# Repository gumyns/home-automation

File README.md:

# Licenses
Code: [Apache 2.0](./LICENSE) ([tl;dr](https://choosealicense.com/licenses/apache-2.0/))

PCB: [CC-BY](./CC-BY.md) ([tl;dr](https://creativecommons.org/licenses/by/4.0/))

# What is it?
STM32 ARM based home automation system. Devices are built with STM32 F0 series microcontrollers (mostly with [STM32F030F4](http://www.st.com/en/microcontrollers/stm32f0x0-value-line.html?querycriteria=productId=LN1826), cheapest one). Project provides also a plugin for [OpenHab2](http://docs.openhab.org/) ([demo](http://demo.openhab.org:8080/start/index)), that allows integration also with other automation systems.

## Architecture
Generally it looks like this:

computer <=> gateway <=> hub <=> device 

On top there's a computer with OpenHab2 running with plugin configured (e.g. PC, RaspberryPi, Odroid, whatever that can run Java8).

Gateway is some cheap ARM based board with Linux, like Rasperry Zero, NanoPi, and communicates with central computer utilizing distributed system built on top of TCP/IP.

Hub is an ARM based board, that can communicate with gateway using any of supported protocols, and can communicate with devices. Amount of ports is configurable.

Device is just a worker (also ARM based board), that communitates with hubs using specific protocol, and provides data to the system.

#### This repository contains following modules
##### - [OpenHab2 plugin](./openhab2)
##### - [C++ server and plugins for gateways](./server)
##### - [PCB layouts and microcontrollers code](./hardware)

# NOTE
This project is in early stage, it's already a working prototype but far from final product.

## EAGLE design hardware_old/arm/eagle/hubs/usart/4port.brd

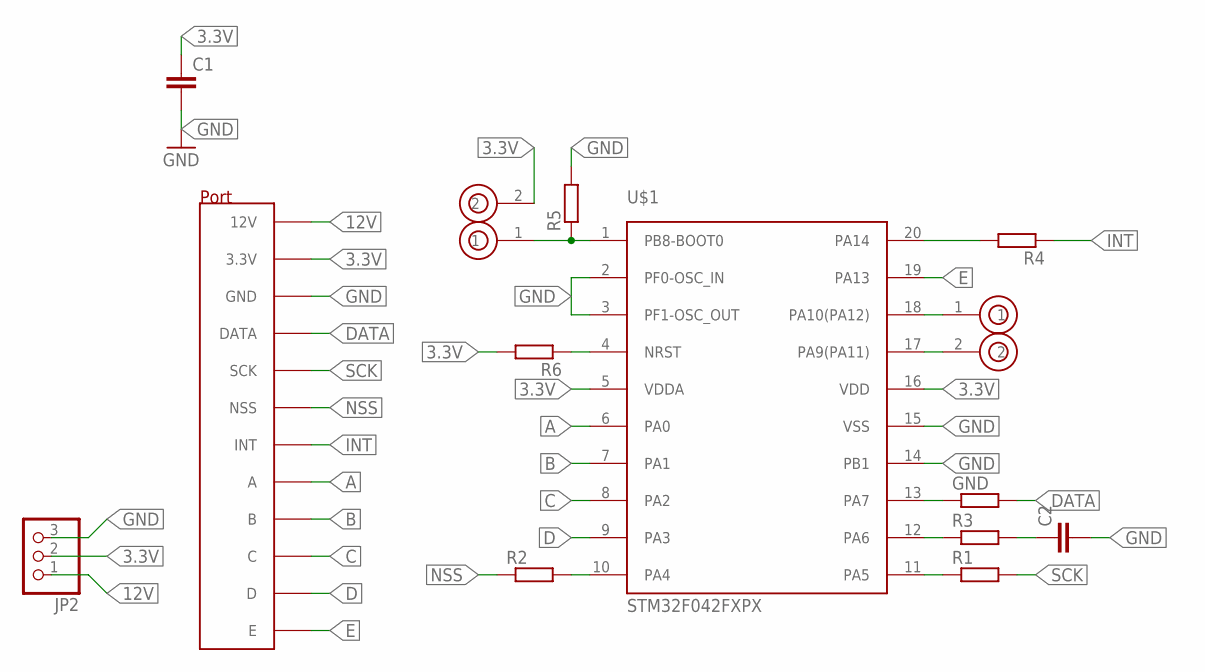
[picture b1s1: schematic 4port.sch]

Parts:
C1, C2: C-EUC1206; C1206
GND: R-EU_R0603; R0603
JP2: PINHD-1X3; 1X03
R1, R2, R3, R4, R5, R6: R-EU_R0603; R0603
U$1: STM32F042FXPX; TSSOP20
U$2, U$3: GOLDPIN_2; GOLDPIN_2_SMD
U$4: HUB_PORT

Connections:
3.3V: C1.1, JP2.2, R6.2, U$1.5 (VDDA), U$1.16 (VDD), U$2.2, U$4.3.3V
12V: JP2.1, U$4.12V
A: U$1.6 (PA0), U$4.A
B: U$1.7 (PA1), U$4.B
C: U$1.8 (PA2), U$4.C
D: U$1.9 (PA3), U$4.D
DATA: GND.2, U$4.DATA
E: U$1.19 (PA13), U$4.E
GND: C1.2, C2.2, JP2.3, R5.2, U$1.2 (PF0-OSC_IN), U$1.3 (PF1-OSC_OUT), U$1.14 (PB1), U$1.15 (VSS), U$4.GND
INT: R4.1, U$4.INT
unnamed: C2.1, R3.2
unnamed: GND.1, U$1.13 (PA7)
unnamed: R3.1, U$1.12 (PA6)
unnamed: R1.1, U$1.11 (PA5)
unnamed: R2.2, U$1.10 (PA4)
unnamed: R6.1, U$1.4 (NRST)
unnamed: R5.1, U$1.1 (PB8-BOOT0), U$2.1
unnamed: U$1.18 (PA10(PA12)), U$3.1
unnamed: U$1.17 (PA9(PA11)), U$3.2
unnamed: R4.2, U$1.20 (PA14)
NSS: R2.1, U$4.NSS
SCK: R1.2, U$4.SCK

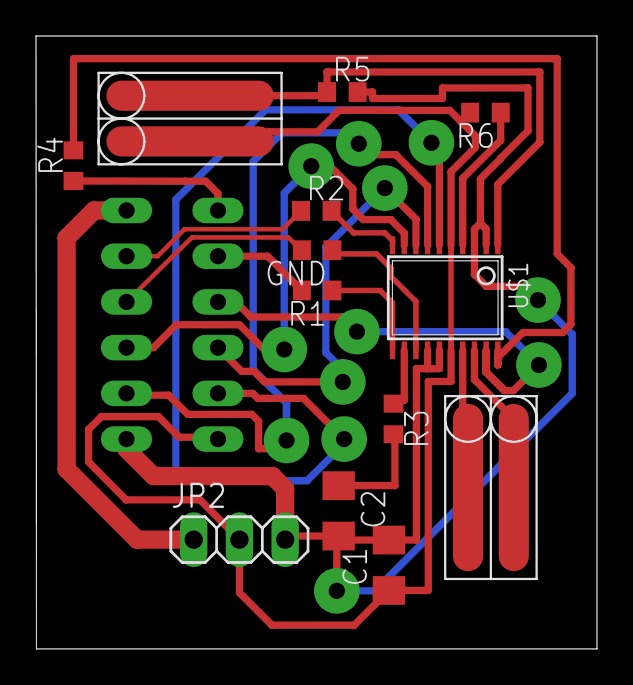
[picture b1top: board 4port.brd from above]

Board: 2 copper layers, 31.2 x 34.1 mm, 14 parts (1 on the bottom side), 22 nets.

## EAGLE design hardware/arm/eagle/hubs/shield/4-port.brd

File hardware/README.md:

## Prerequisites
Download gcc-arm: http://gnuarmeclipse.github.io/toolchain/install/

Generate toolchains and cmake files, call this:
```commandline
python prepare.py
```

Download CubeMX package for STM32F0, or whole STM32CubeMX
```
http://www.st.com/en/embedded-software/stm32cubef0.html
```

## Building
Setup proper toolchain for correct device:
```commandline
mkdir build 
cd build 
cmake .. -DCMAKE_TOOLCHAIN_FILE=../toolchains/STM32F030x6.cmake
```

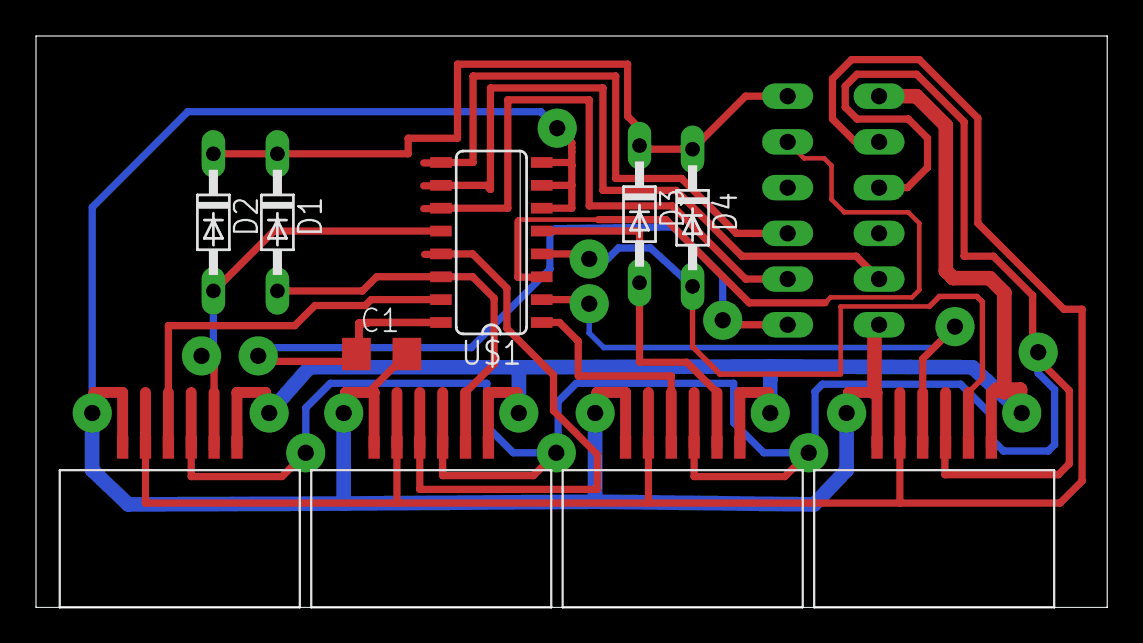
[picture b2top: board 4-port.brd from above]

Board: 2 copper layers, 59.5 x 31.7 mm, 11 parts (0 on the bottom side), 18 nets.

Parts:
C1: C1206
D1, D2, D3, D4: BAS15; DO34-7
U$1: 74HC4051_MUX; SO16
U$2, U$4, U$5, U$7: RJ12SMD; RJ12_SMD
U$3: HUB_PORT

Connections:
3.3V: C1.1, U$1.16, U$3.3.3V
12V: U$2.VCC, U$3.12V, U$4.VCC, U$5.VCC, U$7.VCC
A: U$1.11, U$3.A
B: U$1.10, U$3.B
C: U$1.9, U$3.C
DATA: U$2.DATA, U$3.DATA, U$4.DATA, U$5.DATA, U$7.DATA
GND: C1.2, U$1.6, U$1.7, U$1.8, U$2.GND, U$3.GND, U$4.GND, U$5.GND, U$7.GND
INT: D1.C, D2.C, D3.C, D4.C, U$3.INT
INT0: D1.A, U$1.14, U$2.INT
INT1: D2.A, U$1.12, U$4.INT
INT2: D3.A, U$1.5, U$5.INT
INT3: D4.A, U$1.4, U$7.INT
NSS: U$2.NSS, U$3.NSS, U$4.NSS, U$5.NSS, U$7.NSS
SCK: U$1.3, U$3.SCK
SCK0: U$1.13, U$2.SCK
SCK1: U$1.15, U$4.SCK
SCK2: U$1.1, U$5.SCK
SCK3: U$1.2, U$7.SCK

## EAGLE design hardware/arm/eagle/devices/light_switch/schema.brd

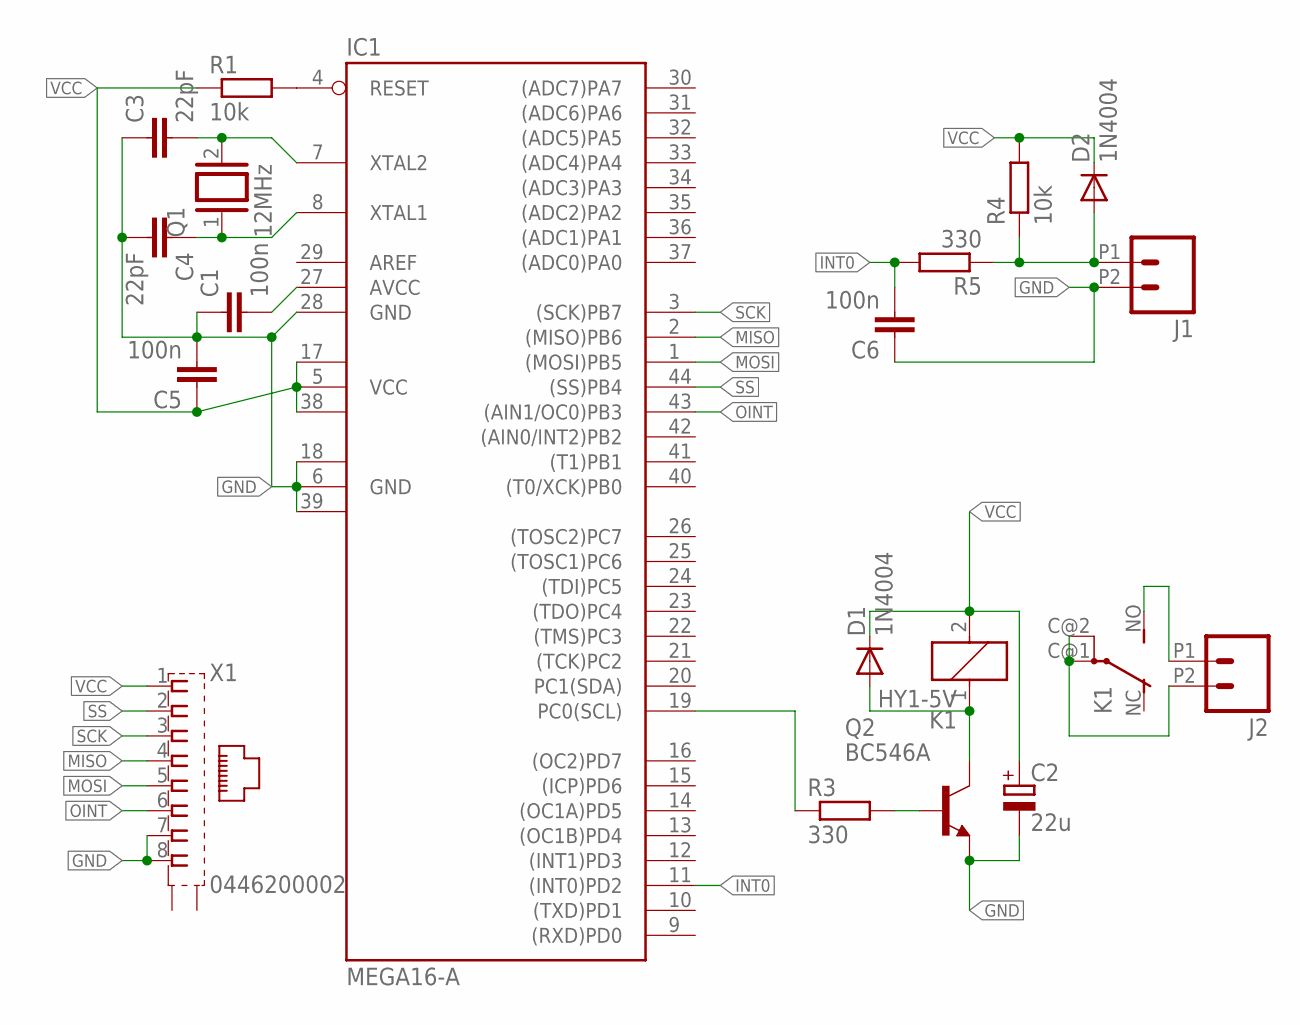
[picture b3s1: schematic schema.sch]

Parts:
C1, C5, C6: 100n; C050-024X044
C2: 22u; E2,5-6
C3, C4: 22pF; C050-024X044
D1, D2: 1N4004; DO41-10
IC1: MEGA16-A; TQFP44
J1, J2: M022.54MM_SCREWTERM; 1X02_2.54_SCREWTERM
K1: HY1-5V; HY
Q1: 12MHz; QS
Q2: BC546A; TO92-EBC
R1, R4: 10k; 0204/7
R3, R5: 330; 0204/7
X1: 0446200002

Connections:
GND: C1.1, C2.-, C3.1, C4.2, C5.2, C6.1, IC1.6 (GND), IC1.18 (GND1), IC1.28 (GND), IC1.39 (GND2), J1.P2 (2), Q2.E, X1.7, X1.8
INT0: C6.2, IC1.11 ((INT0)PD2), R5.2
MISO: IC1.2 ((MISO)PB6), X1.4
MOSI: IC1.1 ((MOSI)PB5), X1.5
unnamed: C3.2, IC1.7 (XTAL2), Q1.2
unnamed: C4.1, IC1.8 (XTAL1), Q1.1
unnamed: D1.A, K1.1, Q2.C
unnamed: Q2.B, R3.2
unnamed: J2.P2 (2), K1.C@1, K1.C@2
unnamed: C1.2, IC1.27 (AVCC)
unnamed: IC1.4 (RESET), R1.2
unnamed: J2.P1 (1), K1.NO (S)
unnamed: IC1.19 (PC0(SCL)), R3.1
unnamed: D2.A, J1.P1 (1), R4.1, R5.1
OINT: IC1.43 ((AIN1/OC0)PB3), X1.6
SCK: IC1.3 ((SCK)PB7), X1.3
SS: IC1.44 ((SS)PB4), X1.2
VCC: C2.+, C5.1, D1.C, D2.C, IC1.5 (VCC), IC1.17 (VCC1), IC1.38 (VCC2), K1.2, R1.1, R4.2, X1.1

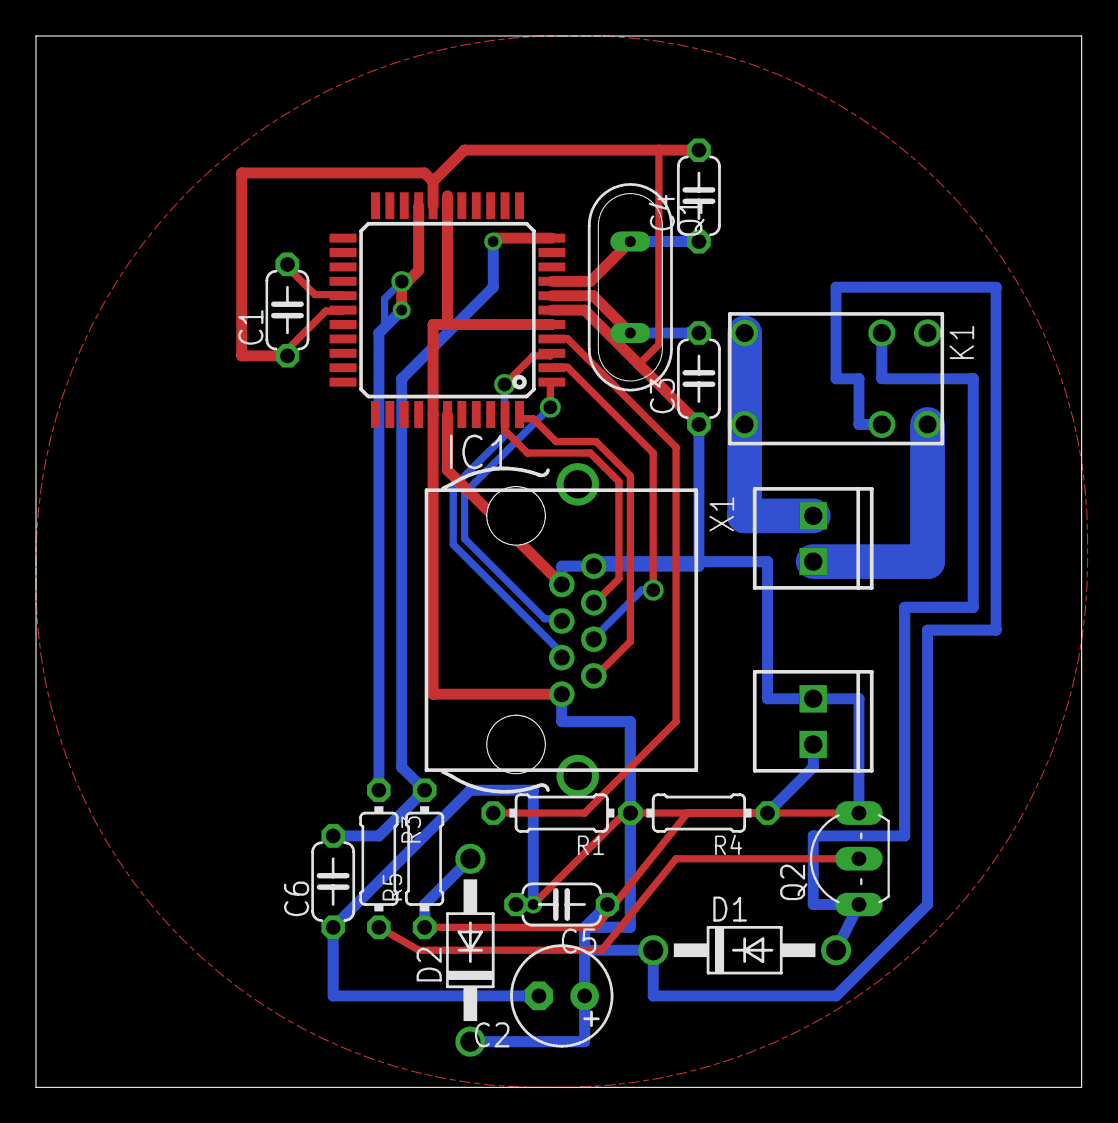
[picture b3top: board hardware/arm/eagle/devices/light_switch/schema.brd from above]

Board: 2 copper layers, 58.1 x 58.4 mm, 19 parts (0 on the bottom side), 18 nets.

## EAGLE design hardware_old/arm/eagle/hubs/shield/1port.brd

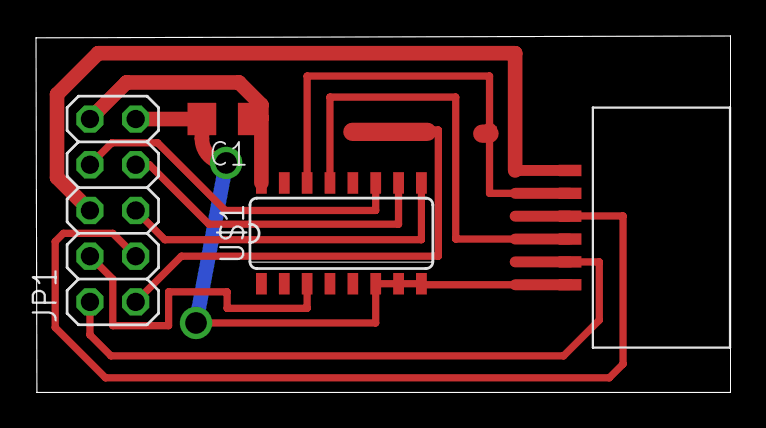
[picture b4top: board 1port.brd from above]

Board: 2 copper layers, 38.6 x 19.8 mm, 5 parts (0 on the bottom side), 12 nets.

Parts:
C1: C1206
JP1: 2X05
U$1: 74HC4051_MUX; SO16
U$4: RJ12SMD; RJ12_SMD
U$9: DIODE; DIL_DIODE_SMD

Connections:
3.3V: C1.1, JP1.10, U$1.16
12V: JP1.6, U$4.VCC
A: JP1.8, U$1.11
B: JP1.7, U$1.10
C: JP1.5, U$1.9
DATA: JP1.3, U$4.DATA
GND: C1.2, JP1.9, U$1.6, U$1.7, U$1.8, U$4.GND
INT: JP1.1, U$9.1
INT0: U$1.14, U$4.INT, U$9.2
NSS: JP1.2, U$4.NSS
SCK: JP1.4, U$1.3
SCK0: U$1.13, U$4.SCK

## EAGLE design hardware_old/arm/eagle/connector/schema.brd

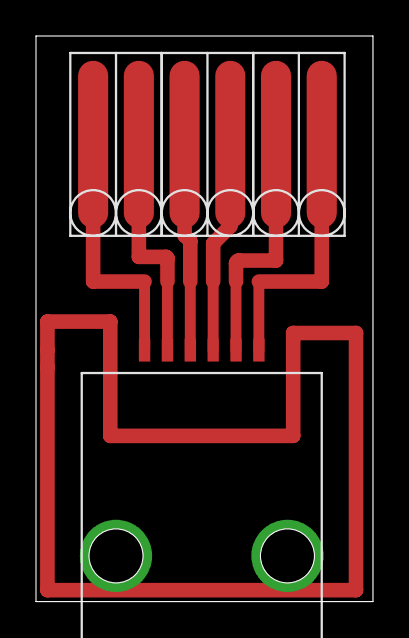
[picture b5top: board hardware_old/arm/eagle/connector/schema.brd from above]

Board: 2 copper layers, 18.7 x 31.4 mm, 4 parts (0 on the bottom side), 6 nets.

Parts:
U$1: RJ12SMD; RJ12_SMD
U$4, U$5, U$6: GOLDPIN_2; GOLDPIN_2_SMD

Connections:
unnamed: U$1.1, U$6.1
unnamed: U$1.2, U$6.2
unnamed: U$1.3, U$5.1
unnamed: U$1.4, U$5.2
unnamed: U$1.5, U$4.1
unnamed: U$1.6, U$4.2

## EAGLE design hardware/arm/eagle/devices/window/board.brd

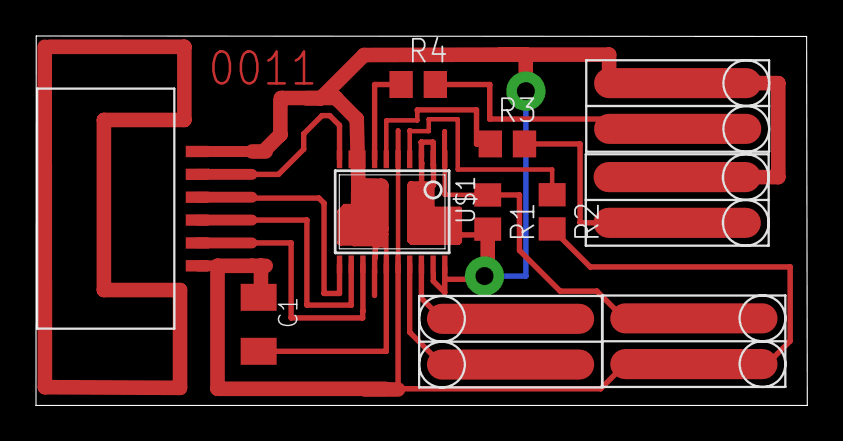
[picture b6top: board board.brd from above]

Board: 2 copper layers, 42.9 x 20.5 mm, 11 parts (0 on the bottom side), 14 nets.

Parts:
C1: 100n; C1206K
R1, R2: 10k; R0805
R3, R4: 2.2k; R0805
U$1: STM32F042FXPX; TSSOP20
U$2: RJ12SMD; RJ12_SMD
U$3, U$4, U$5, U$6: GOLDPIN_2; GOLDPIN_2_SMD

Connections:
GND: C1.2, R1.2, U$1.15, U$2.GND, U$5.2, U$6.2
unnamed: U$1.18, U$3.1
unnamed: U$1.17, U$3.2
unnamed: R2.1, U$1.4
unnamed: R1.1, U$1.1, U$4.2
unnamed: R3.1, U$1.6
unnamed: R4.1, U$1.7
unnamed: R3.2, U$5.1
unnamed: U$1.11, U$2.SCK
unnamed: U$1.13, U$2.INT
unnamed: U$1.10, U$2.NSS
unnamed: R4.2, U$6.1
unnamed: U$1.12, U$2.DATA
VCC: C1.1, R2.2, U$1.5, U$1.16, U$2.VCC, U$4.1

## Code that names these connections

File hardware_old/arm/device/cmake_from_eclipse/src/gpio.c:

/**
  ******************************************************************************
  * File Name          : gpio.c
  * Description        : This file provides code for the configuration
  *                      of all used GPIO pins.
  ******************************************************************************
  *
  * COPYRIGHT(c) 2017 STMicroelectronics
  *
  * Redistribution and use in source and binary forms, with or without modification,
  * are permitted provided that the following conditions are met:
  *   1. Redistributions of source code must retain the above copyright notice,
  *      this list of conditions and the following disclaimer.
  *   2. Redistributions in binary form must reproduce the above copyright notice,
  *      this list of conditions and the following disclaimer in the documentation
  *      and/or other materials provided with the distribution.
  *   3. Neither the name of STMicroelectronics nor the names of its contributors
  *      may be used to endorse or promote products derived from this software
  *      without specific prior written permission.
  *
  * THIS SOFTWARE IS PROVIDED BY THE COPYRIGHT HOLDERS AND CONTRIBUTORS "AS IS"
  * AND ANY EXPRESS OR IMPLIED WARRANTIES, INCLUDING, BUT NOT LIMITED TO, THE
  * IMPLIED WARRANTIES OF MERCHANTABILITY AND FITNESS FOR A PARTICULAR PURPOSE ARE
  * DISCLAIMED. IN NO EVENT SHALL THE COPYRIGHT HOLDER OR CONTRIBUTORS BE LIABLE
  * FOR ANY DIRECT, INDIRECT, INCIDENTAL, SPECIAL, EXEMPLARY, OR CONSEQUENTIAL
  * DAMAGES (INCLUDING, BUT NOT LIMITED TO, PROCUREMENT OF SUBSTITUTE GOODS OR
  * SERVICES; LOSS OF USE, DATA, OR PROFITS; OR BUSINESS INTERRUPTION) HOWEVER
  * CAUSED AND ON ANY THEORY OF LIABILITY, WHETHER IN CONTRACT, STRICT LIABILITY,
  * OR TORT (INCLUDING NEGLIGENCE OR OTHERWISE) ARISING IN ANY WAY OUT OF THE USE
  * OF THIS SOFTWARE, EVEN IF ADVISED OF THE POSSIBILITY OF SUCH DAMAGE.
  *
  ******************************************************************************
  */

/* Includes ------------------------------------------------------------------*/
#include "gpio.h"
/* USER CODE BEGIN 0 */

/* USER CODE END 0 */

/*----------------------------------------------------------------------------*/
/* Configure GPIO                                                             */
/*----------------------------------------------------------------------------*/
/* USER CODE BEGIN 1 */

/* USER CODE END 1 */

/** Configure pins as 
        * Analog 
        * Input 
        * Output
        * EVENT_OUT
        * EXTI
        * Free pins are configured automatically as Analog (this feature is enabled through 
        * the Code Generation settings)
*/
void MX_GPIO_Init(void)
{

  GPIO_InitTypeDef GPIO_InitStruct;

  /* GPIO Ports Clock Enable */
  __HAL_RCC_GPIOF_CLK_ENABLE();
  __HAL_RCC_GPIOA_CLK_ENABLE();
  __HAL_RCC_GPIOB_CLK_ENABLE();

  /*Configure GPIO pins : PF0 PF1 */
  GPIO_InitStruct.Pin = GPIO_PIN_0|GPIO_PIN_1;
  GPIO_InitStruct.Mode = GPIO_MODE_ANALOG;
  GPIO_InitStruct.Pull = GPIO_NOPULL;
  HAL_GPIO_Init(GPIOF, &GPIO_InitStruct);

  /*Configure GPIO pins : PA2 PA3 PA4 PA5 
                           PA6 PA7 PA9 PA10 
                           PA13 PA14 */
  GPIO_InitStruct.Pin = GPIO_PIN_2|GPIO_PIN_3|GPIO_PIN_4|GPIO_PIN_5 
                          |GPIO_PIN_6|GPIO_PIN_7|GPIO_PIN_9|GPIO_PIN_10 
                          |GPIO_PIN_13|GPIO_PIN_14;
  GPIO_InitStruct.Mode = GPIO_MODE_ANALOG;
  GPIO_InitStruct.Pull = GPIO_NOPULL;
  HAL_GPIO_Init(GPIOA, &GPIO_InitStruct);

  /*Configure GPIO pin : PB1 */
  GPIO_InitStruct.Pin = GPIO_PIN_1;
  GPIO_InitStruct.Mode = GPIO_MODE_ANALOG;
  GPIO_InitStruct.Pull = GPIO_NOPULL;
  HAL_GPIO_Init(GPIOB, &GPIO_InitStruct);

}

/* USER CODE BEGIN 2 */

/* USER CODE END 2 */

/**
  * @}
  */

/**
  * @}
  */

/************************ (C) COPYRIGHT STMicroelectronics *****END OF FILE****/

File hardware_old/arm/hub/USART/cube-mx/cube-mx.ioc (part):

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Mcu.Name=STM32F042F4Px
Mcu.Package=TSSOP20
Mcu.UserName=STM32F042F4Px
PA0.GPIOParameters=GPIO_Label
PA0.GPIO_Label=ADDR0
PA0.Signal=GPIO_Output
PA1.GPIOParameters=GPIO_Label
PA1.GPIO_Label=ADDR1
PA1.Signal=GPIO_Output
PA10.Mode=Asynchronous
PA10.Signal=USART1_RX
PA14.Signal=GPXTI14
PA2.GPIOParameters=GPIO_Label
PA2.GPIO_Label=ADDR2
PA2.Signal=GPIO_Output
PA3.GPIOParameters=GPIO_Label
PA3.GPIO_Label=ADDR3
PA3.Signal=GPIO_Output
PA4.Mode=NSS_Signal_Hard_Input
PA4.Signal=SPI1_NSS
PA5.Mode=Simplex_Bidirectional_Master
PA5.Signal=SPI1_SCK
PA7.Mode=Simplex_Bidirectional_Master
PA7.Signal=SPI1_MOSI
PA9.Mode=Asynchronous
PA9.Signal=USART1_TX
RCC.SYSCLKFreq_VALUE=8000000
board=cube-mx

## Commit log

2017-04-01 Update LICENSE
2017-04-01 init
2017-04-01 License
2017-04-01 Create CC-BY
2017-04-01 Rename CC-BY to CC-BY.md
2017-04-01 some info about project
2017-04-02 4 port shield pcb
2017-04-02 updated uart hub pcb
2017-04-04 fixed port address in hub
2017-04-16 some build scripts
2017-04-16 some build scripts
    new file: .gitignore
    new file: 00_boost.py
    new file: 01_json.py
    new file: 02_zeromq.py
    new file: dep_lib.py
    modified: ../resolveDependencies.py
2017-04-16 cleanups, more build scripts
2017-04-16 complete build script for server
2017-04-16 docs
2017-04-16 cleanup
2017-04-17 cmake changes for bigger project support
2017-04-17 same convention used for all factories
2017-04-17 script fix
2017-04-17 make fix
2017-04-17 simplified cmake scrips
2017-04-17 proper config
2017-04-17 build all script + 'tests'
2017-04-17 simplify tests
2017-04-17 preparations for CMake support for embedded code
2017-04-19 arm toolchain generator
2017-04-20 added some working cmake embedded project as reference
2017-04-20 make one common standard library for all embedded projects
2017-04-20 linker scripts
2017-06-13 deprecated old hardware stuff, there will be new soon
2017-06-13 'readme'
2017-06-14 hardware deps
2017-06-23 cmake fix
2017-06-25 toolchain fix
2017-06-25 toolchain generator
2017-06-26 download flashing tool
2017-06-26 arm cmake init
2017-06-27 arm cmake
2017-06-27 toolchain changes
2017-06-27 generate libs directories
2017-06-27 find cmsis and hal added
2017-06-27 gitignore
2017-06-27 window sensor project
2017-06-28 change window sensor to cpp
2017-06-28 added i2c to window sensor
2017-06-28 added scriptable i2c address
2017-06-28 naming change, cleanup
2017-06-28 int pullup
2017-06-28 interrupts
2017-06-29 generate startup files
2017-06-29 add startup files to project
2017-06-29 some cleanups
2017-06-29 build all possible addresses script
2017-06-29 added interrupt
2017-06-29 some improvements to build script
2017-06-30 hub project
2017-08-01 test of usart as main protocol
2017-12-03 kicad templates
2017-12-03 test device board
2017-12-12 board fixes

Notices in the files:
parts and their libraries:
SparkFun-Connectors: Licensing: Creative Commons ShareAlike 4.0 International - https://creativecommons.org/licenses/by-sa/4.0
